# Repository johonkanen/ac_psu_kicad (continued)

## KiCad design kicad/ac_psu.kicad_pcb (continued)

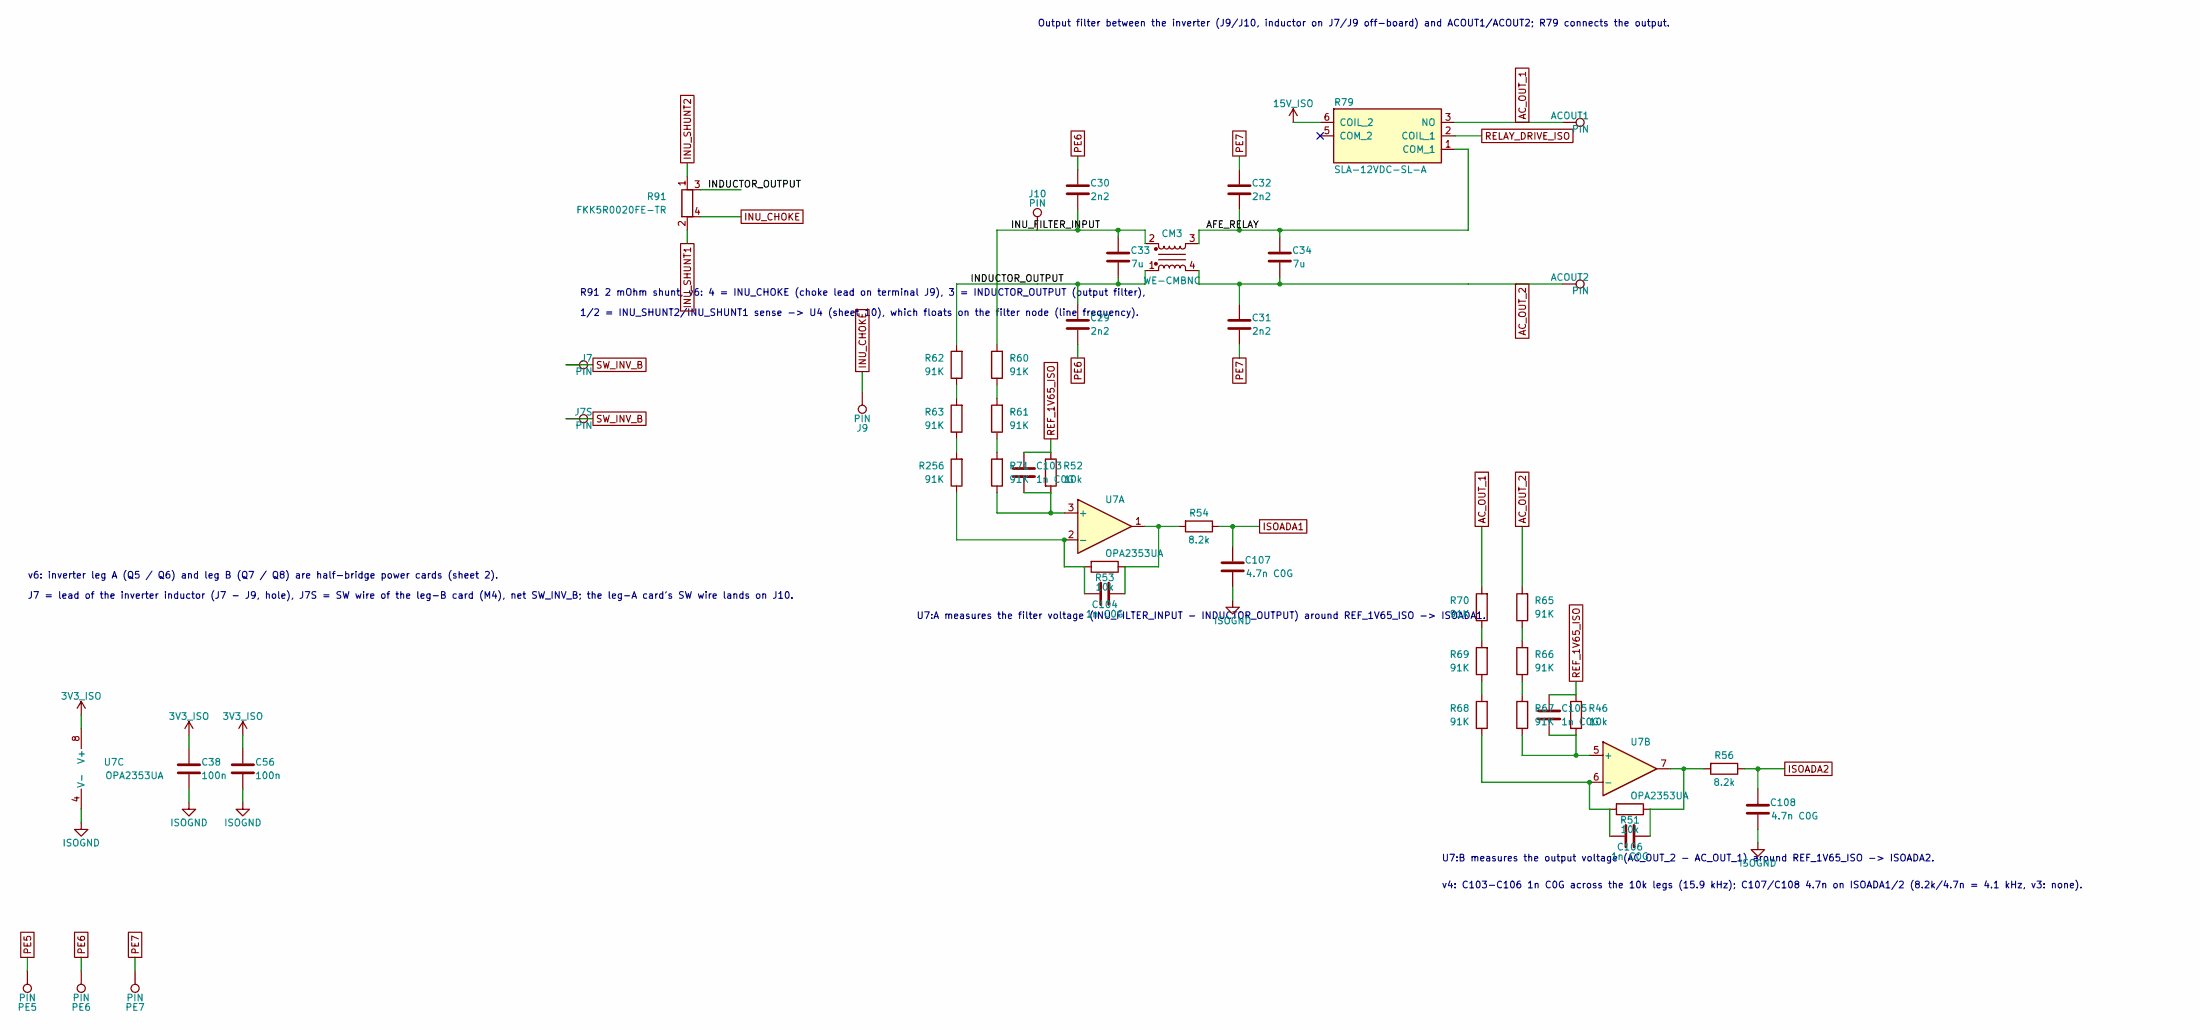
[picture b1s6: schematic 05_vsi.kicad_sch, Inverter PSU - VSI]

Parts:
ACOUT1, ACOUT2: PIN; Terminal_2x1_P5.00mm_D2.0mm_Drill1.4mm
C29, C30, C31, C32: 2n2; C_Disc_D12.5mm_W5.0mm_P7.50mm
C33, C34: 7u; C_Rect_L33.0mm_W20.0mm_P27.50mm_MKS4_Proteus
C38, C56: 100n; C_0402_1005Metric
C103, C104, C105, C106: 1n C0G; C_0402_1005Metric
C107, C108: 4.7n C0G; C_0402_1005Metric
CM3: WE-CMBNC; L_CommonMode_WE-CMBNC
J7, J9: PIN; WireHole_D5.0mm_Drill2.3mm
J7S, J10: PIN; Wuerth_REDCUBE-THR_74650074_M4_PTH
PE5, PE6, PE7: PIN; Terminal_D4.0mm_Drill3.0mm
R46, R51, R52, R53: 10k; R_0402_1005Metric
R54, R56: 8.2k; R_0402_1005Metric
R60, R61, R62, R63, R65, R66, R67, R68, R69, R70, R71, R256: 91K; R_1206_3216Metric_Pad1.30x1.75mm_HandSolder
R79: SLA-12VDC-SL-A; Relay_SLA-12VDC-SL-A
R91: FKK5R0020FE-TR; R_Shunt_FKK5R0020FE
U7: OPA2353UA; TSSOP-8_3x3mm_P0.65mm_Proteus

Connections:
3V3_ISO: C38.2, C56.2, U7.8 (V+); also elsewhere on the board
15V_ISO: R79.6 (COIL_2); also elsewhere on the board
/05 VSI/AFE_RELAY: C32.2, C34.1, CM3.3, R79.1 (COM_1)
/05 VSI/INDUCTOR_OUTPUT: C29.2, C33.2, CM3.1, R62.2, R91.3
/05 VSI/INU_FILTER_INPUT: C30.2, C33.1, CM3.2, J10.1, R60.2
AC_OUT_1: ACOUT1.1, R70.2, R79.3 (NO)
AC_OUT_2: ACOUT2.1, C31.2, C34.2, CM3.4, R65.2
INU_CHOKE: J9.1, R91.4
INU_SHUNT1: R91.2; also elsewhere on the board
INU_SHUNT2: R91.1; also elsewhere on the board
ISOADA1: C107.1, R54.1; also elsewhere on the board
ISOADA2: C108.1, R56.1; also elsewhere on the board
ISOGND: C38.1, C56.1, C107.2, C108.2, U7.4 (V-); also elsewhere on the board
unnamed: C104.1, R53.1, R54.2, U7.1
unnamed: C106.1, R51.1, R56.2, U7.7
unnamed: R60.1, R61.2
unnamed: R61.1, R71.2
unnamed: R62.1, R63.2
unnamed: R65.1, R66.2
unnamed: R66.1, R67.2
unnamed: R68.2, R69.1
unnamed: R69.2, R70.1
unnamed: R63.1, R256.2
unnamed: C103.2, R52.2, R71.1, U7.3 (+)
unnamed: C104.2, R53.2, R256.1, U7.2 (-)
unnamed: C105.2, R46.2, R67.1, U7.5 (+)
unnamed: C106.2, R51.2, R68.1, U7.6 (-)
PE5: PE5.1; also elsewhere on the board
PE6: C29.1, C30.1, PE6.1
PE7: C31.1, C32.1, PE7.1
REF_1V65_ISO: C103.1, C105.1, R46.1, R52.1; also elsewhere on the board
RELAY_DRIVE_ISO: R79.2 (COIL_1); also elsewhere on the board
SW_INV_B: J7.1, J7S.1

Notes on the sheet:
v6: inverter leg A (Q5 / Q6) and leg B (Q7 / Q8) are half-bridge power cards (sheet 2).
R91 2 mOhm shunt, v6: 4 = INU_CHOKE (choke lead on terminal J9), 3 = INDUCTOR_OUTPUT (output filter),
1/2 = INU_SHUNT2/INU_SHUNT1 sense -> U4 (sheet 10), which floats on the filter node (line frequency).
J7 = lead of the inverter inductor (J7 - J9, hole), J7S = SW wire of the leg-B card (M4), net SW_INV_B; the leg-A card's SW wire lands on J10.
Output filter between the inverter (J9/J10, inductor on J7/J9 off-board) and ACOUT1/ACOUT2; R79 connects the output.
U7:A measures the filter voltage (INU_FILTER_INPUT - INDUCTOR_OUTPUT) around REF_1V65_ISO -> ISOADA1.
v4: C103-C106 1n C0G across the 10k legs (15.9 kHz); C107/C108 4.7n on ISOADA1/2 (8.2k/4.7n = 4.1 kHz, v3: none).
U7:B measures the output voltage (AC_OUT_2 - AC_OUT_1) around REF_1V65_ISO -> ISOADA2.

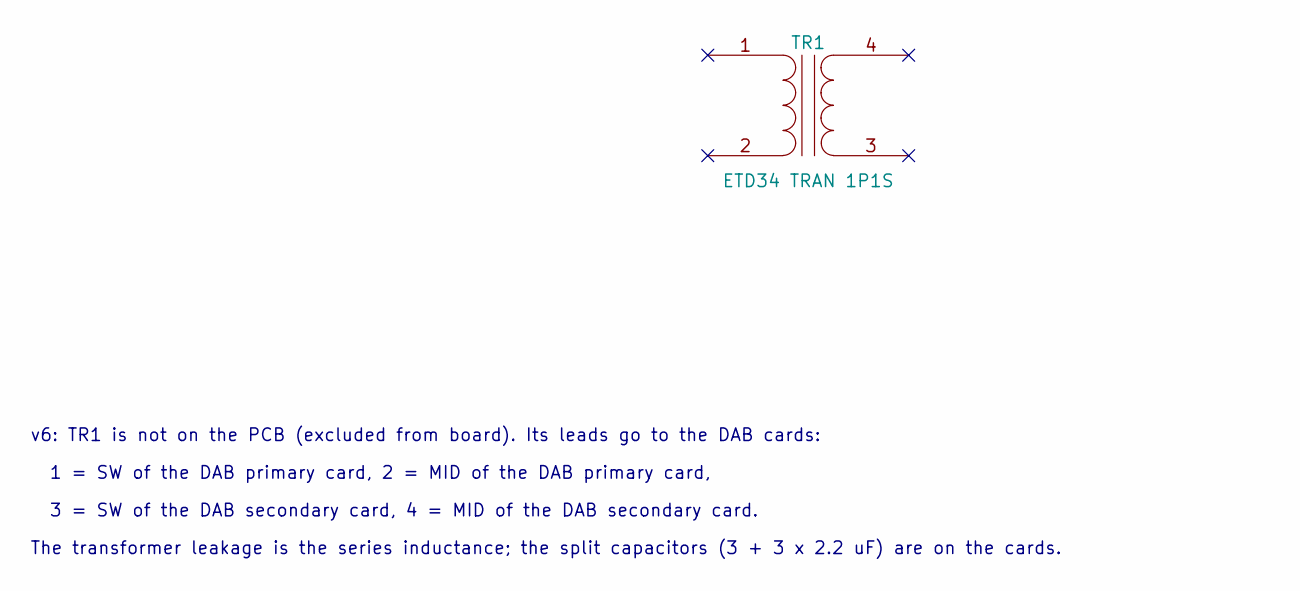
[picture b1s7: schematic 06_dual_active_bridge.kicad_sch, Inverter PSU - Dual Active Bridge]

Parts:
TR1: ETD34 TRAN 1P1S

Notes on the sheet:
v6: TR1 is not on the PCB (excluded from board). Its leads go to the DAB cards:
1 = SW of the DAB primary card, 2 = MID of the DAB primary card,
3 = SW of the DAB secondary card, 4 = MID of the DAB secondary card.
The transformer leakage is the series inductance; the split capacitors (3 + 3 x 2.2 uF) are on the cards.

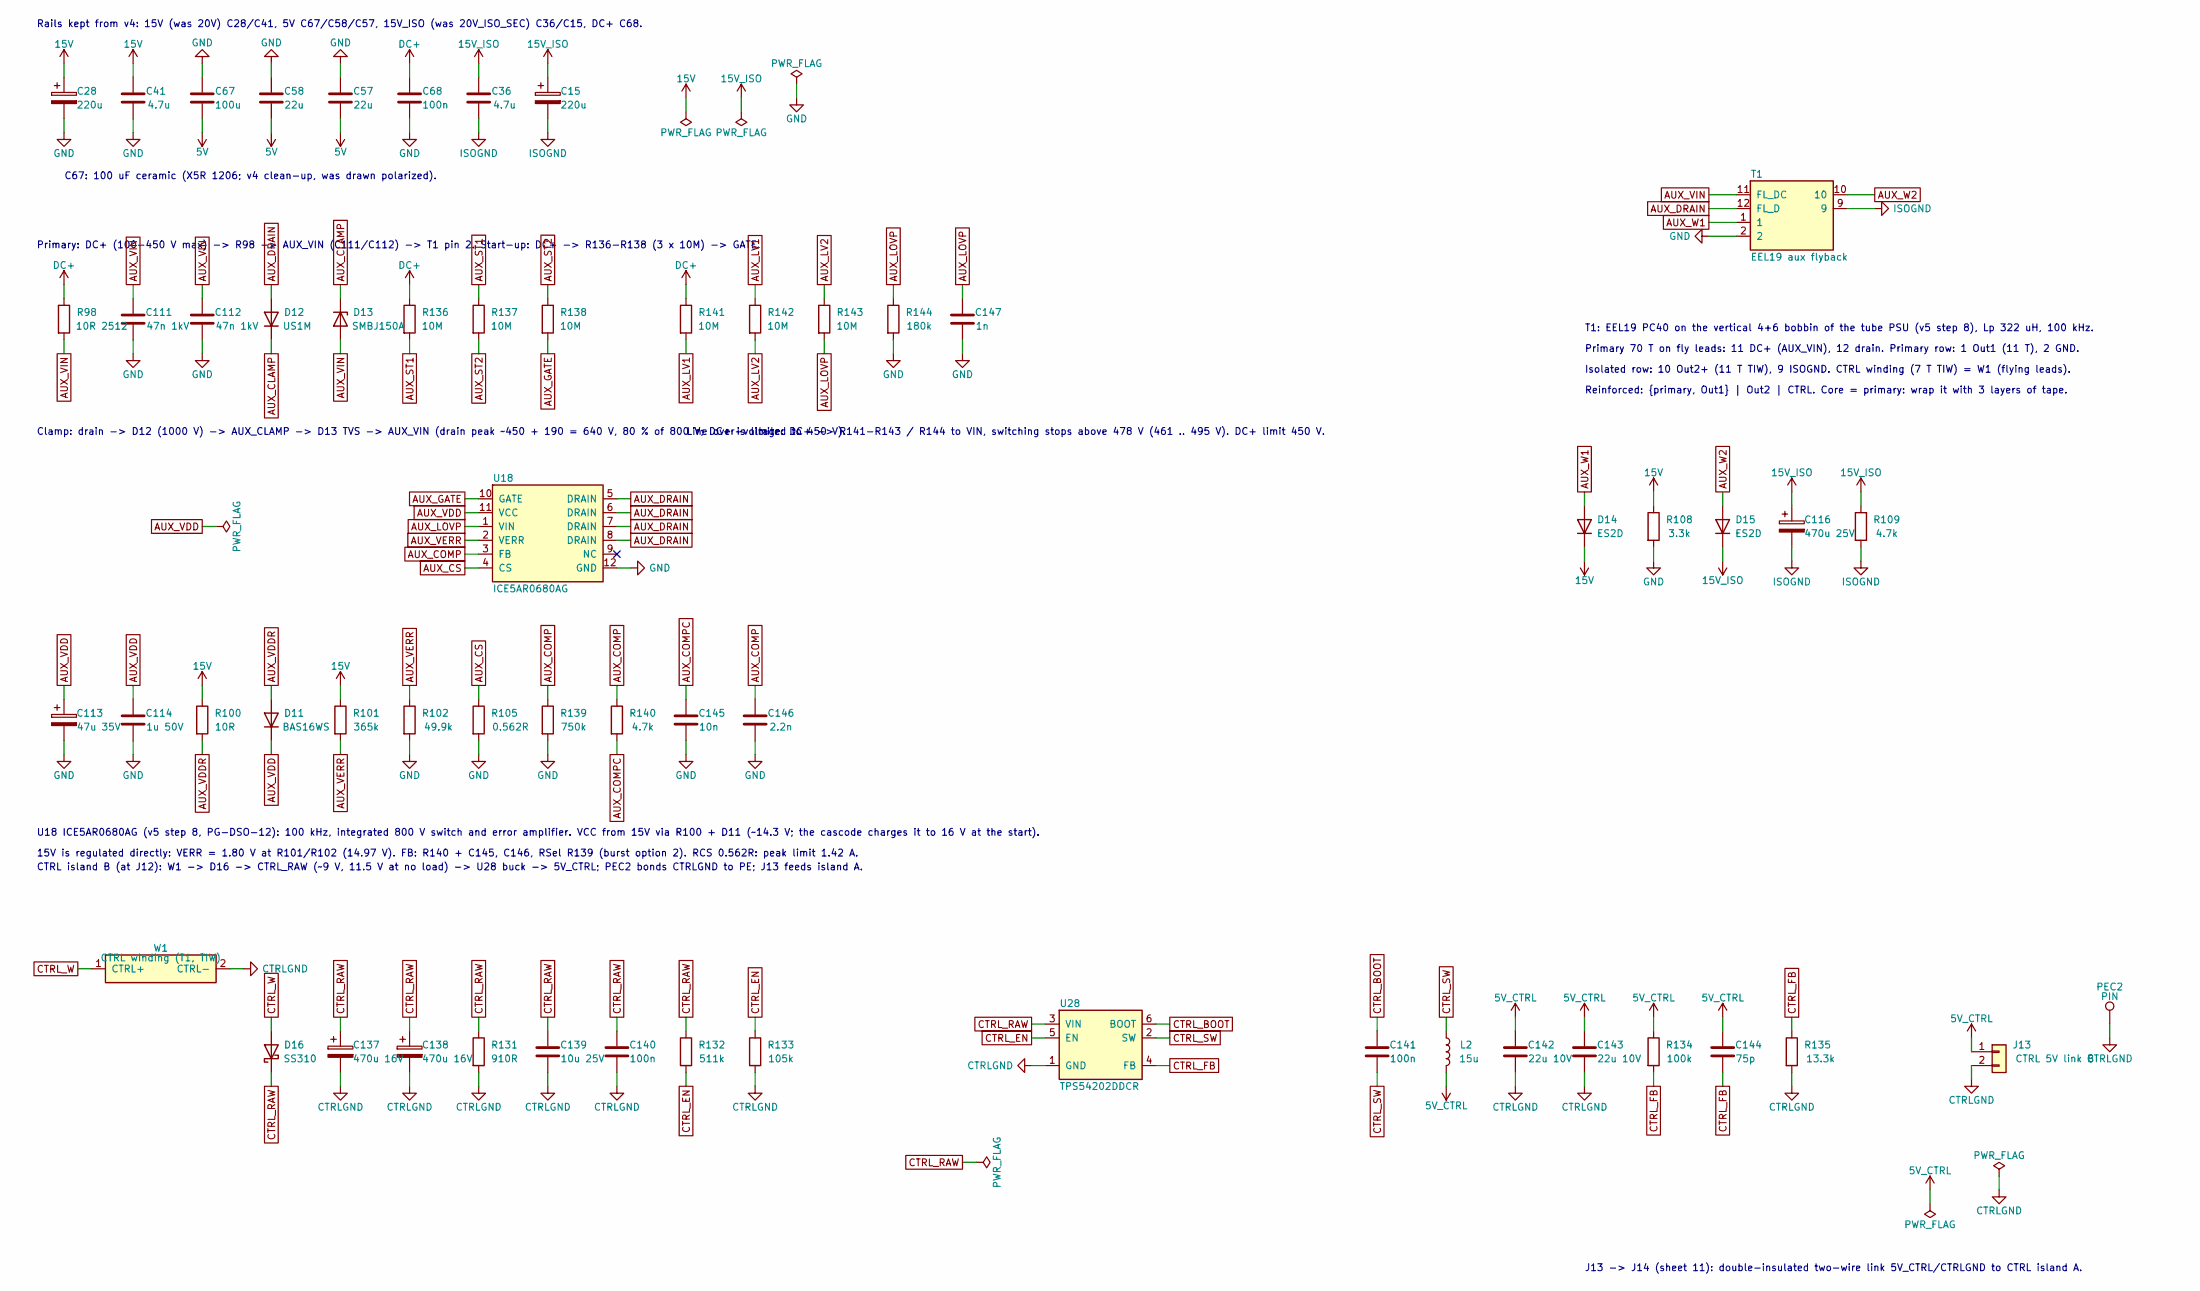
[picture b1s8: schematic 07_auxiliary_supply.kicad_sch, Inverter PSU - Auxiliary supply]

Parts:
C15, C28: 220u; CP_Elec_6.3x7.7_EEEFTE221XAP
C36, C41: 4.7u; C_1206_3216Metric_Pad1.33x1.80mm_HandSolder
C57, C58: 22u; C_1206_3216Metric_Pad1.33x1.80mm_HandSolder
C67: 100u; C_1206_3216Metric_Pad1.33x1.80mm_HandSolder
C68: 100n; C_1206_3216Metric_Pad1.33x1.80mm_HandSolder
C111, C112: 47n 1kV; C_1210_3225Metric
C113: 47u 35V; CP_Elec_6.3x5.4
C114: 1u 50V; C_0603_1608Metric
C116: 470u 25V; CP_Elec_8x10
C137, C138: 470u 16V; CP_Elec_8x10
C139: 10u 25V; C_1206_3216Metric
C140, C141: 100n; C_0603_1608Metric
C142, C143: 22u 10V; C_1206_3216Metric
C144: 75p; C_0603_1608Metric
C145: 10n; C_0603_1608Metric
C146: 2.2n; C_0603_1608Metric
C147: 1n; C_0603_1608Metric
D11: BAS16WS; D_SOD-323_AC
D12: US1M; D_SMA_AC
D13: SMBJ150A; D_SMB_AC
D14, D15: ES2D; D_SMA_AC
D16: SS310; D_SMA_AC
J13: CTRL 5V link B; PinHeader_1x02_P2.54mm_Vertical
L2: 15u; L_Sunlord_SWPA6045S
PEC2: PIN; Terminal_D4.0mm_Drill3.0mm
R98: 10R 2512; R_2512_6332Metric
R100: 10R; R_0603_1608Metric
R101: 365k; R_0603_1608Metric
R102: 49.9k; R_0603_1608Metric
R105: 0.562R; R_1206_3216Metric
R108: 3.3k; R_0805_2012Metric
R109: 4.7k; R_0805_2012Metric
R131: 910R; R_1206_3216Metric
R132: 511k; R_0603_1608Metric
R133: 105k; R_0603_1608Metric
R134: 100k; R_0603_1608Metric
R135: 13.3k; R_0603_1608Metric
R136, R137, R138, R141, R142, R143: 10M; R_1206_3216Metric
R139: 750k; R_0603_1608Metric
R140: 4.7k; R_0603_1608Metric
R144: 180k; R_0603_1608Metric
T1: EEL19 aux flyback; Transformer_EEL19_V_4+6_SideLeads
U18: ICE5AR0680AG; Infineon_PG-DSO-12_CoolSET
U28: TPS54202DDCR; SOT-23-6
W1: CTRL winding (T1, TIW); CTRL_Winding_Leads_2x1.6mm_P5.08mm

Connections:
5V: C57.2, C58.2, C67.2; also elsewhere on the board
5V_CTRL: C142.1, C143.1, C144.1, J13.1, L2.2, R134.1; also elsewhere on the board
15V: C28.1, C41.1, D14.C (K), R100.1, R101.1, R108.1; also elsewhere on the board
15V_ISO: C15.1, C36.1, C116.1, D15.C (K), R109.1; also elsewhere on the board
AUX_CLAMP: D12.C (K), D13.C (K)
AUX_COMP: C146.1, R139.1, R140.1, U18.3 (FB)
AUX_COMPC: C145.1, R140.2
AUX_CS: R105.1, U18.4 (CS)
AUX_DRAIN: D12.A, T1.12 (FL_D), U18.5 (DRAIN), U18.6 (DRAIN), U18.7 (DRAIN), U18.8 (DRAIN)
AUX_GATE: R138.2, U18.10 (GATE)
AUX_LOVP: C147.1, R143.2, R144.1, U18.1 (VIN)
AUX_LV1: R141.2, R142.1
AUX_LV2: R142.2, R143.1
AUX_ST1: R136.2, R137.1
AUX_ST2: R137.2, R138.1
AUX_VDD: C113.1, C114.1, D11.C (K), U18.11 (VCC)
AUX_VDDR: D11.A, R100.2
AUX_VERR: R101.2, R102.1, U18.2 (VERR)
AUX_VIN: C111.1, C112.1, D13.A, R98.2, T1.11 (FL_DC)
AUX_W1: D14.A, T1.1
AUX_W2: D15.A, T1.10
CTRLGND: C137.2, C138.2, C139.2, C140.2, C142.2, C143.2, J13.2, PEC2.1, R131.2, R133.2, R135.2, U28.1 (GND), W1.2 (CTRL-); also elsewhere on the board
CTRL_BOOT: C141.1, U28.6 (BOOT)
CTRL_EN: R132.2, R133.1, U28.5 (EN)
CTRL_FB: C144.2, R134.2, R135.1, U28.4 (FB)
CTRL_RAW: C137.1, C138.1, C139.1, C140.1, D16.C (K), R131.1, R132.1, U28.3 (VIN)
CTRL_SW: C141.2, L2.1, U28.2 (SW)
CTRL_W: D16.A, W1.1 (CTRL+)
DC+: C68.2, R98.1, R136.1, R141.1; also elsewhere on the board
GND: C28.2, C41.2, C57.1, C58.1, C67.1, C68.1, C111.2, C112.2, C113.2, C114.2, C145.2, C146.2, C147.2, R102.2, R105.2, R108.2, R139.2, R144.2, T1.2, U18.12 (GND); also elsewhere on the board
ISOGND: C15.2, C36.2, C116.2, R109.2, T1.9; also elsewhere on the board

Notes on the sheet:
Rails kept from v4: 15V (was 20V) C28/C41, 5V C67/C58/C57, 15V_ISO (was 20V_ISO_SEC) C36/C15, DC+ C68.
C67: 100 uF ceramic (X5R 1206; v4 clean-up, was drawn polarized).
Primary: DC+ (100-450 V max) -> R98 -> AUX_VIN (C111/C112) -> T1 pin 2. Start-up: DC+ -> R136-R138 (3 x 10M) -> GATE.
Clamp: drain -> D12 (1000 V) -> AUX_CLAMP -> D13 TVS -> AUX_VIN (drain peak ~450 + 190 = 640 V, 80 % of 800 V; DC+ is limited to 450 V).
Line over-voltage: DC+ -> R141-R143 / R144 to VIN, switching stops above 478 V (461 .. 495 V). DC+ limit 450 V.
U18 ICE5AR0680AG (v5 step 8, PG-DSO-12): 100 kHz, integrated 800 V switch and error amplifier. VCC from 15V via R100 + D11 (~14.3 V; the cascode charges it to 16 V at the start).
15V is regulated directly: VERR = 1.80 V at R101/R102 (14.97 V). FB: R140 + C145, C146, RSel R139 (burst option 2). RCS 0.562R: peak limit 1.42 A.
T1: EEL19 PC40 on the vertical 4+6 bobbin of the tube PSU (v5 step 8), Lp 322 uH, 100 kHz.
Primary 70 T on fly leads: 11 DC+ (AUX_VIN), 12 drain. Primary row: 1 Out1 (11 T), 2 GND.
Isolated row: 10 Out2+ (11 T TIW), 9 ISOGND. CTRL winding (7 T TIW) = W1 (flying leads).
Reinforced: {primary, Out1} | Out2 | CTRL. Core = primary: wrap it with 3 layers of tape.
CTRL island B (at J12): W1 -> D16 -> CTRL_RAW (~9 V, 11.5 V at no load) -> U28 buck -> 5V_CTRL; PEC2 bonds CTRLGND to PE; J13 feeds island A.
J13 -> J14 (sheet 11): double-insulated two-wire link 5V_CTRL/CTRLGND to CTRL island A.

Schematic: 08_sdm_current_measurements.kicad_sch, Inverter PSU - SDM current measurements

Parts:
C52, C53, C74, C75: 220p; C_0603_1608Metric
C64, C80: 100n; C_0402_1005Metric
C71, C73, C76, C77: 100n; C_0603_1608Metric
C91, C92: 100n C0G; C_1206_3216Metric
C160: 1u; C_0603_1608Metric
C161: 1u 25V; C_0603_1608Metric
D8, D17: MM3Z5V1T1; D_SOD-323_AC
R55, R72: 33R; R_0402_1005Metric
R57, R58, R73, R74: 12.4R; R_0402_1005Metric
R59, R75: 470R; R_0805_2012Metric_Pad1.20x1.40mm_HandSolder
R64: FKK5R0020FE-TR; R_Shunt_FKK5R0020FE
R257: 390R; R_1206_3216Metric
U5, U6: ADUM7701-8BRIZ-RL7; SOIC-8W_7.5x5.85mm_P1.27mm_ADuM7701
U29: B0512S-1WR3; Converter_DCDC_Mornsun_B05xxS-1WR3_SIP-4

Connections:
3V3_ISO: C80.2, U6.8 (VDD2); also elsewhere on the board
5V: C160.1, U29.1 (Vin); also elsewhere on the board
15V_ISO: R257.1; also elsewhere on the board
ADCLK: U5.7 (MCLKIN); also elsewhere on the board
ADCLK_DAB: U6.7 (MCLKIN); also elsewhere on the board
DAB_GROUND: R64.4; also elsewhere on the board
DAB_SHUNT1: R64.2, R73.2
DAB_SHUNT2: C74.2, C75.2, C76.2, C77.2, D17.A, R64.1, R74.2, U6.4 (GND1)
GND: C64.1, C160.2, U5.5 (GND2), U29.2 (GND); also elsewhere on the board
ISOGND: C80.1, U6.5 (GND2); also elsewhere on the board
ISOPGND: R64.3; also elsewhere on the board
ISO_DAB_SDM_RAW_VOLTAGE: R75.2, R257.2
MDATA: R55.2; also elsewhere on the board
MDATA_DAB: R72.2; also elsewhere on the board
unnamed: C71.1, C73.1, D8.C (K), R59.1, U5.1 (VDD1)
unnamed: C76.1, C77.1, D17.C (K), R75.1, U6.1 (VDD1)
unnamed: R55.1, U5.6 (MDAT)
unnamed: C53.1, C91.1, R57.1, U5.2 (VIN+)
unnamed: C52.1, C91.2, R58.1, U5.3 (VIN-)
unnamed: R72.1, U6.6 (MDAT)
unnamed: C75.1, C92.1, R73.1, U6.2 (VIN+)
unnamed: C74.1, C92.2, R74.1, U6.3 (VIN-)
SDM_RAW_VOLTAGE: C161.1, R59.2, U29.6 (+Vo)
SHUNT1: C52.2, C53.2, C71.2, C73.2, C161.2, D8.A, R58.2, U5.4 (GND1), U29.4 (0V); also elsewhere on the board
SHUNT2: R57.2; also elsewhere on the board
VCC: C64.2, U5.8 (VDD2); also elsewhere on the board

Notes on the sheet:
v4: C91 100n C0G (1206) across VIN+/VIN- compensates the shunt inductance:
tau = L/R = 2.5 us; with 100 nF use R_leg = 2.5 Ohm per nH of shunt L (4 nH -> 10R, 5 nH -> 12.4R, 6 nH -> 15R).
U5 floats on the AFE shunt R48 (sheet 1): GND1 = SHUNT1 (R48 sense pin 1), VDD1 = 5.1 V from D8 via R59.
v4: C92 100n C0G (1206) across VIN+/VIN- compensates the shunt inductance:
U6 floats on the DAB shunt R64: GND1 = DAB_SHUNT2.
R64: 2 mOhm Kelvin shunt between ISOPGND and the DAB secondary ground DAB_GROUND (DC- terminal J42 of the DAB secondary card).
v6: U6 VDD1 = 5.1 V (D17) from 15V_ISO through R257 + R75: 11.5 .. 13.8 mA at 15 .. 17 V.
v6: U5 now floats at the filter end of the AFE leg-1 choke (R48, sheet 1); VDD1 from U29 through R59 / D8.

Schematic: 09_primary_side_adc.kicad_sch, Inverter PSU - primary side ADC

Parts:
AD1: ADS7056; X2QFN-8_1.5x1.5mm_P0.5mm_ADS7056
C9: 1n; C_0402_1005Metric
C17, C18: 100n; C_0402_1005Metric
C39: 1u; C_0402_1005Metric
C88, C89: 4.7n C0G; C_0402_1005Metric
L1: 22uH; L_0805_2012Metric
R86: 10R; R_0402_1005Metric
R87: RESISTOR_ARRAY; R_Array_Convex_4x0402_Proteus
U11: SN74LV4051; TSSOP-16_4.4x5mm_P0.65mm_Proteus
U12: TLV316IDBVR; SOT-23-5_TLV316

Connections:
ADA0: U11.15 (X2)
ADA1: U11.14 (X1); also elsewhere on the board
ADA2: C88.1, U11.13 (X0); also elsewhere on the board
ADA3: C89.1, U11.12 (X3); also elsewhere on the board
ADA4: U11.1 (X4)
ADA5: U11.2 (X6)
ADA6: U11.4 (X7)
ADASEL0: U11.11 (A); also elsewhere on the board
ADASEL1: U11.10 (B); also elsewhere on the board
ADASEL2: U11.9 (C); also elsewhere on the board
CLK1: R87.3 (R3.1); also elsewhere on the board
CS1: R87.1 (R1.1); also elsewhere on the board
GND: AD1.5 (GND), AD1.8 (AINM), C9.1, C17.1, C18.1, C39.1, C88.2, C89.2, U11.5 (X5), U11.6 (INH), U11.7 (VEE), U11.8 (VSS), U12.2 (V-); also elsewhere on the board
unnamed: AD1.7 (AINP), C9.2, R86.1
unnamed: AD1.4 (DVDD), AD1.6 (AVDD), C17.2, C18.2, L1.1, U12.5 (V+)
unnamed: AD1.3 (SCLK), R87.6 (R3.2)
unnamed: AD1.2 (SDO), R87.7 (R2.2)
unnamed: AD1.1 (~CS), R87.8 (R1.2)
unnamed: U11.3 (X), U12.3 (+)
unnamed: R86.2, U12.1, U12.4 (-)
SDATA1: R87.2 (R2.1); also elsewhere on the board
VCC: C39.2, L1.2, U11.16 (VDD); also elsewhere on the board

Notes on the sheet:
AGND and DC- in the Proteus schematic are both net GND; 3V3 = VCC.
v4: INH (pin 6) tied to GND (v3: single-pin net DGND, floating).
VDD = 3V3 (VCC), VEE = VSS = AGND (GND).
check logic
v4: C88/C89 4.7n C0G (0402) with R18/R9 8.2k filter ADA2/ADA3 at 4.1 kHz; placed next to U11.
R87:D (pads 4/5) has no net in the Proteus layout.

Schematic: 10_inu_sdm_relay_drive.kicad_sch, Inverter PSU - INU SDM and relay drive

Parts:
C37: 100n; C_0402_1005Metric
C43, C44, C55, C78: 100n; C_0603_1608Metric
C51, C54: 220p; C_0603_1608Metric
C90: 100n C0G; C_1206_3216Metric
C162: 1u; C_0603_1608Metric
C163: 1u 25V; C_0603_1608Metric
D3, D4, D5, D10: ZLLS400TA; D_SOD-323_AC
D9: MM3Z5V1T1; D_SOD-323_AC
Q13, Q14: 2N7000; SOT-23_Proteus
R50: 33R; R_0402_1005Metric
R78, R88, R89, R90: 2.2k; R_0603_1608Metric
R92, R93: 12.4R; R_0402_1005Metric
R94: 470R; R_0805_2012Metric_Pad1.20x1.40mm_HandSolder
U4: ADUM7701-8BRIZ-RL7; SOIC-8W_7.5x5.85mm_P1.27mm_ADuM7701
U30: B0512S-1WR3; Converter_DCDC_Mornsun_B05xxS-1WR3_SIP-4

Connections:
3V3_ISO: C37.2, U4.8 (VDD2); also elsewhere on the board
5V_ISOL: C162.1, U30.1 (Vin); also elsewhere on the board
15V: D10.C (K); also elsewhere on the board
15V_ISO: D4.C (K); also elsewhere on the board
GND: C44.2, Q14.3 (S), R90.2; also elsewhere on the board
GPIO_BYPASS_RLY: R89.2, R90.1; also elsewhere on the board
GPIO_BYPASS_RLY_ISO: R78.2, R88.1; also elsewhere on the board
INU_ADCLK: U4.7 (MCLKIN); also elsewhere on the board
INU_SHUNT1: R92.2; also elsewhere on the board
INU_SHUNT2: C51.2, C54.2, C55.2, C78.2, C163.2, D9.A, R93.2, U4.4 (GND1), U30.4 (0V); also elsewhere on the board
ISOGND: C37.1, C43.2, C162.2, Q13.3 (S), R88.2, U4.5 (GND2), U30.2 (GND); also elsewhere on the board
ISO_AFE_SDM_RAW_VOLTAGE: C163.1, R94.2, U30.6 (+Vo)
MDATA_INU: R50.2; also elsewhere on the board
unnamed: D3.C (K), D4.A
unnamed: D5.C (K), D10.A
unnamed: C55.1, C78.1, D9.C (K), R94.1, U4.1 (VDD1)
unnamed: C43.1, Q13.2 (G), R78.1
unnamed: C44.1, Q14.2 (G), R89.1
unnamed: R50.1, U4.6 (MDAT)
unnamed: C54.1, C90.1, R92.1, U4.2 (VIN+)
unnamed: C51.1, C90.2, R93.1, U4.3 (VIN-)
RELAY_DRIVE: D5.A, Q14.1 (D); also elsewhere on the board
RELAY_DRIVE_ISO: D3.A, Q13.1 (D); also elsewhere on the board

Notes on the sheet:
v4: C90 100n C0G (1206) across VIN+/VIN- compensates the shunt inductance:
tau = L/R = 2.5 us; with 100 nF use R_leg = 2.5 Ohm per nH of shunt L (4 nH -> 10R, 5 nH -> 12.4R, 6 nH -> 15R).
VDD1/GND1 of U4 float on the INU shunt: VDD1 is 5.1 V from D9 via R94 (Proteus auto-named nets), GND1 = INU_SHUNT2.
Relay drivers: RELAY_DRIVE -> R20 coil (sheet 1), RELAY_DRIVE_ISO -> R79 coil (sheet 5).
v6: U4 now floats at the output end of the inverter choke (R91, sheet 5); VDD1 from U30 through R94 / D9.

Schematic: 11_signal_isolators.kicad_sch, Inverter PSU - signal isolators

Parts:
C81, C82, C83, C84, C85, C86, C117, C118, C119, C120, C121, C122, C123, C124, C125, C126, C127, C128, C132, C133: 100n; C_0402_1005Metric
C129, C130: 4.7n C0G; C_0402_1005Metric
C131: 10n C0G; C_0402_1005Metric
C134: 10n; C_0402_1005Metric
C135: 2.2u; C_0603_1608Metric
C136: 1u; C_0603_1608Metric
J14: CTRL 5V link A; PinHeader_1x02_P2.54mm_Vertical
PEC1: PIN; Terminal_D4.0mm_Drill3.0mm
R22: 39R; R_0402_1005Metric
R110, R112, R114: 6.8k 0.1%; R_0603_1608Metric
R111, R113, R115, R116, R118, R120, R122, R124, R126: 10k 0.1%; R_0603_1608Metric
R117, R119, R121, R123, R125, R127: 24.9k 0.1%; R_0603_1608Metric
R128, R129, R130: 8.2k; R_0402_1005Metric
R258: 33R; R_0603_1608Metric
U13, U15: Si8661BD-B-IS; SOIC-16W_7.5x10.3mm_P1.27mm_Proteus
U16: Si8660BD-B-IS; SOIC-16W_7.5x10.3mm_P1.27mm_Proteus
U19, U20: ISO7760FDWR; SOIC-16W_7.5x10.3mm_P1.27mm
U21: CA-IS3742LW; SOIC-16W_7.5x10.3mm_P1.27mm
U22, U23, U24: AMC1311BDWVR; SOIC-8_7.5x5.85mm_P1.27mm
U25, U26: OPA2350EA; VSSOP-8_3x3mm_P0.65mm
U27: TPS73033DBVT; SOT-23-5

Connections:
3V3_CTRL: C82.2, C83.2, C86.2, C117.1, C119.1, C121.1, C124.1, C126.1, C128.1, C132.1, C133.1, C135.1, U13.1 (VDD1), U15.1 (VDD1), U16.1 (VDD1), U19.1 (VCC1), U20.1 (VCC1), U21.1 (VDDA), U21.7 (ENA), U22.8 (VDD2), U23.8 (VDD2), U24.8 (VDD2), U25.8 (V+), U26.8 (V+), U27.5 (OUT)
3V3_ISO: C118.1, C120.1, C122.1, C123.1, C125.1, C127.1, U19.16 (VCC2), U20.16 (VCC2), U21.10 (ENB), U21.16 (VDDB), U22.1 (VDD1), U23.1 (VDD1), U24.1 (VDD1); also elsewhere on the board
5V_CTRL_A: C136.1, J14.1, U27.1 (IN), U27.3 (EN)
ADASEL0: U15.15 (B1); also elsewhere on the board
ADASEL0_ISO: U15.2 (A1); also elsewhere on the board
ADASEL1: U15.14 (B2); also elsewhere on the board
ADASEL1_ISO: U15.3 (A2); also elsewhere on the board
ADASEL2: U15.13 (B3); also elsewhere on the board
ADASEL2_ISO: U15.4 (A3); also elsewhere on the board
ADCLK: R22.2; also elsewhere on the board
ADCLK_DAB: U21.13 (B2); also elsewhere on the board
ADCLK_DAB_CTRL: U21.4 (A2); also elsewhere on the board
ADCLK_ISO: U15.6 (A5); also elsewhere on the board
CLK1: U13.12 (B4); also elsewhere on the board
CLK1_ISO: U13.5 (A4); also elsewhere on the board
CS1: U13.11 (B5); also elsewhere on the board
CS1_ISO: U13.6 (A5); also elsewhere on the board
CTRLGND_A: C82.1, C83.1, C86.1, C117.2, C119.2, C121.2, C124.2, C126.2, C128.2, C129.2, C130.2, C131.2, C132.2, C133.2, C134.2, C135.2, C136.2, J14.2, PEC1.1, R119.2, R123.2, R127.2, U13.8 (GND1), U15.8 (GND1), U16.8 (GND1), U19.3 (INB), U19.4 (INC), U19.8 (GND1), U20.8 (GND1), U21.2 (GNDA), U21.8 (GNDA), U22.5 (GND2), U23.5 (GND2), U24.5 (GND2), U25.4 (V-), U26.4 (V-), U26.5 (+), U27.2 (GND); also elsewhere on the board
CTRL_NR: C134.1, U27.4 (NR)
DAB_PWM_HI_SEC: U20.15 (OUTA); also elsewhere on the board
DAB_PWM_HI_SEC_CTRL: U20.2 (INA); also elsewhere on the board
DAB_PWM_LO_SEC: U20.14 (OUTB); also elsewhere on the board
DAB_PWM_LO_SEC_CTRL: U20.3 (INB); also elsewhere on the board
DAB_PWM_PRI_HI: U16.14 (B2); also elsewhere on the board
DAB_PWM_PRI_HI_ISO: U16.3 (A2); also elsewhere on the board
DAB_PWM_PRI_LO: U16.15 (B1); also elsewhere on the board
DAB_PWM_PRI_LO_ISO: U16.2 (A1); also elsewhere on the board
GND: C81.1, C84.1, C85.1, U13.9 (GND2), U15.9 (GND2), U16.9 (GND2); also elsewhere on the board
GPIO_BYPASS_RLY: U15.12 (B4); also elsewhere on the board
GPIO_BYPASS_RLY_ISO: U19.15 (OUTA); also elsewhere on the board
GPIO_BYPASS_RLY_ISOLATED: U15.5 (A4); also elsewhere on the board
GPIO_BYPASS_RLY_ISO_CTRL: U19.2 (INA); also elsewhere on the board
INU_ADCLK: R258.2; also elsewhere on the board
INU_ADCLK_CTRL: U21.3 (A1); also elsewhere on the board
INU_ADCLK_U21: R258.1, U21.14 (B1)
ISOADA1: R110.1; also elsewhere on the board
ISOADA1_AIN: R110.2, R111.1, U22.2 (IN)
ISOADA1_CTRL: C129.1, R128.2; also elsewhere on the board
ISOADA1_M: R116.2, R117.1, U25.2 (-)
ISOADA1_N: R116.1, U22.6 (OUTN)
ISOADA1_OUT: R117.2, R128.1, U25.1
ISOADA1_P: R118.1, U22.7 (OUTP)
ISOADA1_PL: R118.2, R119.1, U25.3 (+)
ISOADA2: R112.1; also elsewhere on the board
ISOADA2_AIN: R112.2, R113.1, U23.2 (IN)
ISOADA2_CTRL: C130.1, R129.2; also elsewhere on the board
ISOADA2_M: R120.2, R121.1, U25.6 (-)
ISOADA2_N: R120.1, U23.6 (OUTN)
ISOADA2_OUT: R121.2, R129.1, U25.7
ISOADA2_P: R122.1, U23.7 (OUTP)
ISOADA2_PL: R122.2, R123.1, U25.5 (+)
ISOADA3: R114.1; also elsewhere on the board
ISOADA3_AIN: R114.2, R115.1, U24.2 (IN)
ISOADA3_CTRL: C131.1, R130.2; also elsewhere on the board
ISOADA3_M: R124.2, R125.1, U26.2 (-)
ISOADA3_N: R124.1, U24.6 (OUTN)
ISOADA3_OUT: R125.2, R130.1, U26.1
ISOADA3_P: R126.1, U24.7 (OUTP)
ISOADA3_PL: R126.2, R127.1, U26.3 (+)
ISOGND: C118.2, C120.2, C122.2, C123.2, C125.2, C127.2, R111.2, R113.2, R115.2, U19.9 (GND2), U20.9 (GND2), U21.9 (GNDB), U21.15 (GNDB), U22.3 (SHTDN), U22.4 (GND1), U23.3 (SHTDN), U23.4 (GND1), U24.3 (SHTDN), U24.4 (GND1); also elsewhere on the board
MDATA: U15.10 (B6); also elsewhere on the board
MDATA_DAB: U21.11 (B4); also elsewhere on the board
MDATA_DAB_CTRL: U21.6 (A4); also elsewhere on the board
MDATA_INU: U21.12 (B3); also elsewhere on the board
MDATA_INU_CTRL: U21.5 (A3); also elsewhere on the board
MDATA_ISO: U15.7 (A6); also elsewhere on the board
unnamed: R22.1, U15.11 (B5)
OPA_SPARE: U26.6 (-), U26.7
PWM_G1: U16.12 (B4); also elsewhere on the board
PWM_G1_ISO: U16.5 (A4); also elsewhere on the board
PWM_G2: U16.11 (B5); also elsewhere on the board
PWM_G2_ISO: U16.6 (A5); also elsewhere on the board
PWM_G3: U16.13 (B3); also elsewhere on the board
PWM_G3_ISO: U16.4 (A3); also elsewhere on the board
PWM_G4: U16.10 (B6); also elsewhere on the board
PWM_G4_ISO: U16.7 (A6); also elsewhere on the board
PWM_Q5: U20.12 (OUTD); also elsewhere on the board
PWM_Q5_CTRL: U20.5 (IND); also elsewhere on the board
PWM_Q6: U19.12 (OUTD); also elsewhere on the board
PWM_Q6_CTRL: U19.5 (IND); also elsewhere on the board
PWM_Q7: U20.11 (OUTE); also elsewhere on the board
PWM_Q7_CTRL: U20.6 (INE); also elsewhere on the board
PWM_Q8: U19.11 (OUTE); also elsewhere on the board
PWM_Q8_CTRL: U19.6 (INE); also elsewhere on the board
PWM_TRANS1: U13.13 (B3); also elsewhere on the board
PWM_TRANS1_ISO: U13.4 (A3); also elsewhere on the board
PWM_TRANS2: U13.14 (B2); also elsewhere on the board
PWM_TRANS2_ISO: U13.3 (A2); also elsewhere on the board
PWM_TRANS3: U13.15 (B1); also elsewhere on the board
PWM_TRANS3_ISO: U13.2 (A1); also elsewhere on the board
PWM_TRANS4: U20.13 (OUTC); also elsewhere on the board
PWM_TRANS4_CTRL: U20.4 (INC); also elsewhere on the board
PWM_TRANS5: U19.10 (OUTF); also elsewhere on the board
PWM_TRANS5_CTRL: U19.7 (INF); also elsewhere on the board
PWM_TRANS6: U20.10 (OUTF); also elsewhere on the board
PWM_TRANS6_CTRL: U20.7 (INF); also elsewhere on the board
SDATA1: U13.10 (B6); also elsewhere on the board
SDATA1_ISO: U13.7 (A6); also elsewhere on the board
VCC: C81.2, C84.2, C85.2, U13.16 (VDD2), U15.16 (VDD2), U16.16 (VDD2); also elsewhere on the board

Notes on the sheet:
3V3 / DC- terminals in the Proteus schematic = nets VCC / GND.
v5: the isolated side of U15/U13/U16 is CTRL island A (3V3_CTRL / CTRLGND_A; was 3V3_ISO / ISOGND).
v5 CTRL island A: ISO-side PWMs / relay (U19, U20), U4/U6 sigma-delta lines (U21), ISOADA1-3 (U22-U26). Side 1 = CTRL (J11), side 2 = ISO.
U19 INB/INC unused (tied to CTRLGND_A), OUTB/OUTC open.
v6: R258 33R in INU_ADCLK at the U21 output (the run to U4 at J9 is over 100 mm).
U21: clocks CTRL -> ISO (U4/U6 MCLKIN), data ISO -> CTRL; firmware samples MDATA_INU/MDATA_DAB with the same phase offset as MDATA_ISO.
C117/C119/C121: CTRL sides of U19/U20/U21, C118/C120/C122: ISO sides.
ISOADAn (U7/U2 output via 8.2k + filter C, sheets 4/5) -> 6.8k/10k (x0.4, <= 1.32 V) -> AMC1311 (gain 1) ->
difference amp 24.9k/10k (x2.49) -> 8.2k + 4.7n/4.7n/10n -> J11: overall x0.996, 0-3.3 V as before.
U26B spare: + to CTRLGND_A, follower.
J14 <- J13 (sheet 7): 5V_CTRL from island B over a double-insulated two-wire link; PEC1 bonds CTRLGND_A to PE.

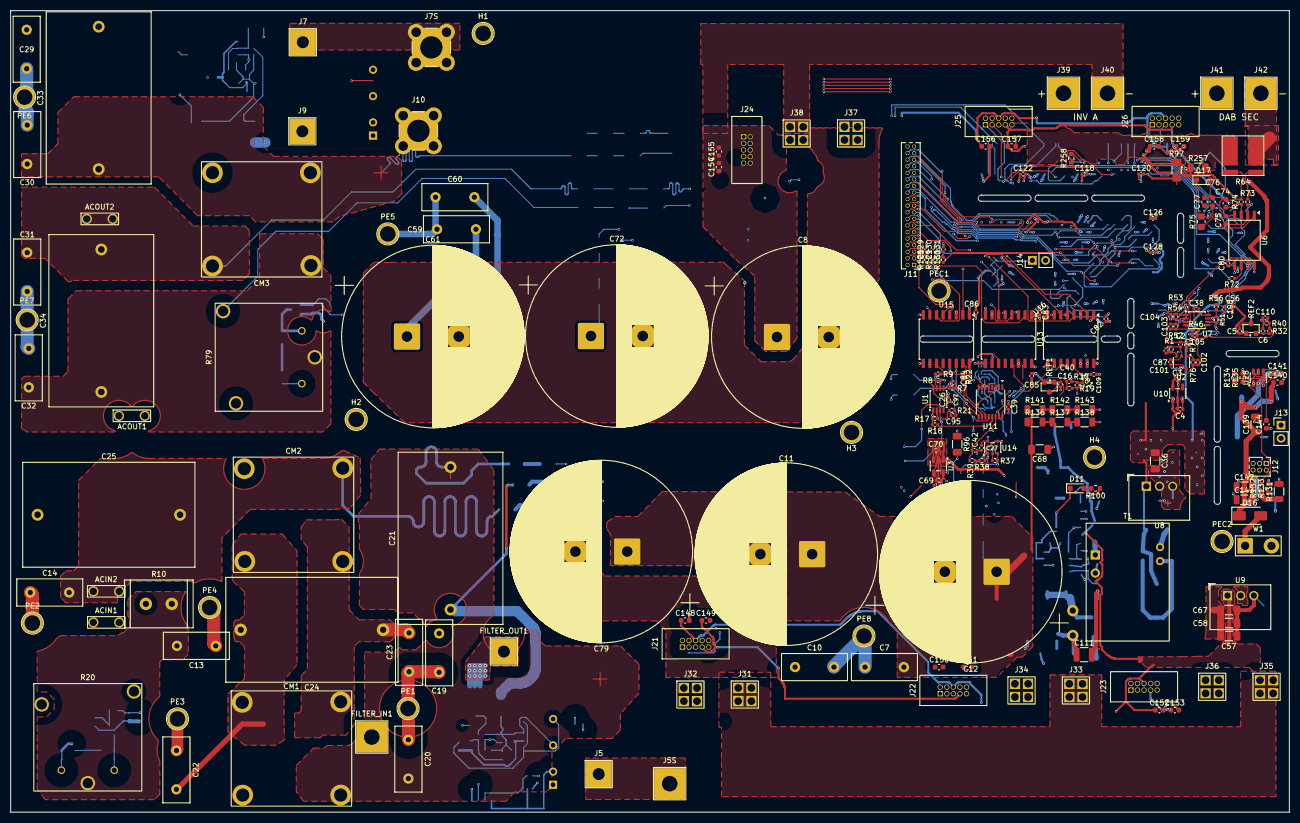
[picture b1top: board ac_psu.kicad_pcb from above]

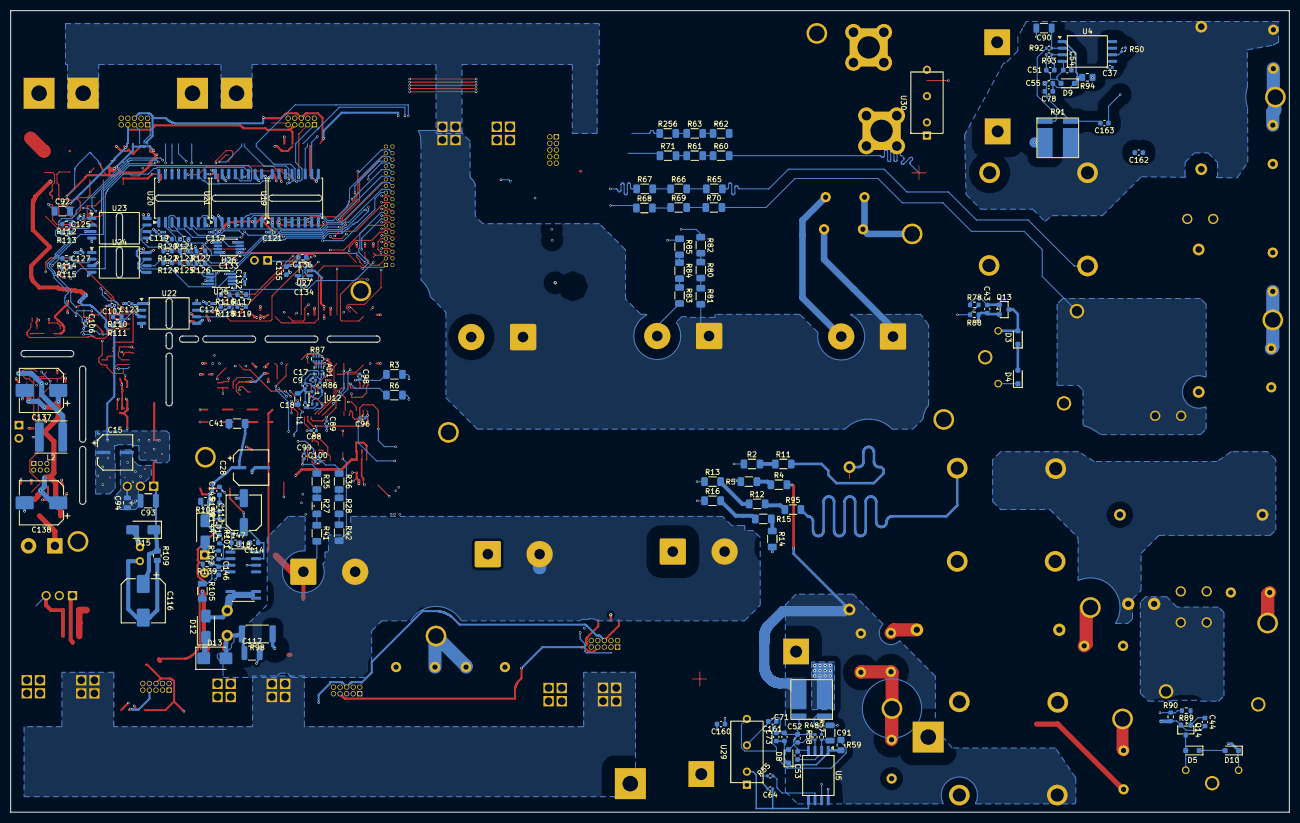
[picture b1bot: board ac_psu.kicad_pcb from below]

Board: 6 copper layers, 246.8 x 154.7 mm, 381 parts (165 on the bottom side), 240 nets.

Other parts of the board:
H1, H2, H3, H4: MountingHole_3.0mm; Terminal_D4.0mm_Drill3.0mm

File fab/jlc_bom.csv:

Comment,Designator,Footprint,JLCPCB Part #
10k,"R1,R7,R8,R17,R21,R37,R38,R46,R51,R52,R53,R76",0402,C25744
39R,R22,0402,C2909354
820R,"R30,R40",0402,C54920831
8.2k,"R9,R18,R39,R54,R56,R77,R128,R129,R130",0402,C25924
33R,"R50,R55,R72",0402,C25105
10R,R86,0402,C25077
12.4R,"R57,R58,R73,R74,R92,R93",0402,C477607
2.2k,"R78,R88,R89,R90",0603,C4190
470R,"R59,R75,R94",0805,C17710
91k,"R2,R3,R4,R5,R6,R11,R12,R13,R14,R15,R16,R27,R28,R35,R36,R41,R42,R60,R61,R62,R63,R65,R66,R67,R68,R69,R70,R71,R80,R81,R82,R83,R84,R85,R95,R256",1206,C2933767
0R,"R96,R97",1206,C17888
1nF,C9,0402,C1523
1nF C0G,"C95,C96,C97,C98,C99,C100,C101,C102,C103,C104,C105,C106",0402,C307441
4.7nF C0G,"C88,C89,C107,C108,C129,C130",0402,C1518204
10nF C0G,"C2,C42,C131",0402,C22400107
100nF,"C3,C4,C17,C18,C26,C27,C37,C38,C56,C64,C69,C70,C80,C81,C82,C83,C84,C85,C86,C87,C109,C110,C117,C118,C119,C120,C121,C122,C123,C124,C125,C126,C127,C128,C132,C133",0402,C1525
1uF,"C5,C6,C16,C39,C40",0402,C52923
100nF,"C43,C44,C55,C71,C73,C76,C77,C78,C140,C141",0603,C14663
220pF,"C51,C52,C53,C54,C74,C75",0603,C1603
100nF C0G,"C90,C91,C92",1206,C170182
4.7uF,"C36,C41",1206,C29823
22uF,"C57,C58,C142,C143",1206,C12891
100uF,C67,1206,C883598
2.2uF 450V,"C1,C35,C45,C46,C47,C48,C49,C50",2220,C445674
22uH,L1,0805,C32375
EEEFTE221XAP,"C15,C28",CP_Elec_6.3x7.7,C190724
ZLLS400TA,"D3,D4,D5,D10",SOD-323,C460267
MM3Z5V1T1G,"D8,D9",SOD-323,C75074
2N7002,"Q13,Q14",SOT-23,C8545
REF3125AIDBZR (alt. for REF3025AIDBZR),"REF1,REF2",SOT-23,C33297
OPA2350EA/2K5 (alt. for OPA2353EA),"U1,U7,U25,U26",VSSOP-8,C115876
TLV316IDBVR,"U2,U12,U14",SOT-23-5,C575578
TPS73033DBVR,"U3,U10,U27",SOT-23-5,C57424
SN74LV4051APWR,U11,TSSOP-16,C7793
ISO7760FDWR (alt. for Si8660BD-B-IS),"U16,U19,U20",SOIC-16W,C2878538
422R,"R19,R32",0402,C67237
33R x4,R87,4D02 0402x4 convex,C25501
AMC1306M05DWVR (alt. for ADuM7701-8BRIZ),"U4,U5,U6",SOIC-8W 300mil,C701717
CA-IS3761LW (alt. for Si8661BD-B-IS),"U13,U15",SOIC-16W,C528659
100nF 500V,C68,1206,C5448934
10uF 50V X7R,C93,1210,C138687
22uF 10V X5R,C94,0805,C29277
10R 2W,R98,2512,C3013385
10R,R100,0603,C22859
365k,R101,0603,C23031
49.9k,R102,0603,C23184
10M,"R136,R137,R138,R141,R142,R143",1206,C26119
180k,R144,0603,C22827
750k,R139,0603,C23240
4.7k,R140,0603,C23162
0.56R (alt. for 0.562R),R105,1206,C2907358
4.7k,R109,0805,C17673
3.3k,R108,0805,C26010
910R,R131,1206,C2930433
511k,R132,0603,C23194
105k,R133,0603,C16840
100k,R134,0603,C25803
13.3k,R135,0603,C25952
6.8k 0.1% 25ppm,"R110,R112,R114",0603,C861539
10k 0.1% 25ppm,"R111,R113,R115,R116,R118,R120,R122,R124,R126",0603,C95204
24.9k 0.1% 25ppm,"R117,R119,R121,R123,R125,R127",0603,C136967
47nF 1kV X7R,"C111,C112",1210,C54916903
47uF 35V electrolytic,C113,CP_Elec_6.3x5.4,C2836440
10nF,C145,0603,C57112
2.2nF,C146,0603,C1604
1nF,C147,0603,C1588
10uF 25V X7R,C139,1206,C14860
75pF C0G,C144,0603,C282074
10nF,C134,0402,C15195
2.2uF,C135,0603,C23630
1uF 50V,"C136,C114",0603,C15849
470uF 25V polymer,C116,CP_Elec_8x10,C46550466
ICE5AR0680AGXUMA1 (pin-compatible: ICE5GR4780AG / 2280AG / 1680AG at lower power),U18,PG-DSO-12,C17699638
470uF 16V polymer,"C137,C138",CP_Elec_8x10,C46550462
15uH SWPA6045S150MT,L2,SWPA6045S,C83374
CA-IS3742LW,U21,SOIC-16W,C4944981
AMC1311BDWVR,"U22,U23,U24",SOIC-8W 300mil,C783598
TPS54202DDCR,U28,SOT-23-6,C191884
BAS16WSQ,D11,SOD-323,C2942457
US1M,D12,SMA,C412437
SMBJ150A,D13,SMB,C123818
ES2DA (ES2D),"D14,D15",SMA,C698723
SS310,D16,SMA,C15874
